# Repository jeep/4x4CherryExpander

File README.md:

# 4x4CherryExpander
4x4 Cherry MX expansion board.

This is the schematic and brd file for a 4x4 matrix of Cherry MX keys with an MCP2300x 8 bit IO Expander.

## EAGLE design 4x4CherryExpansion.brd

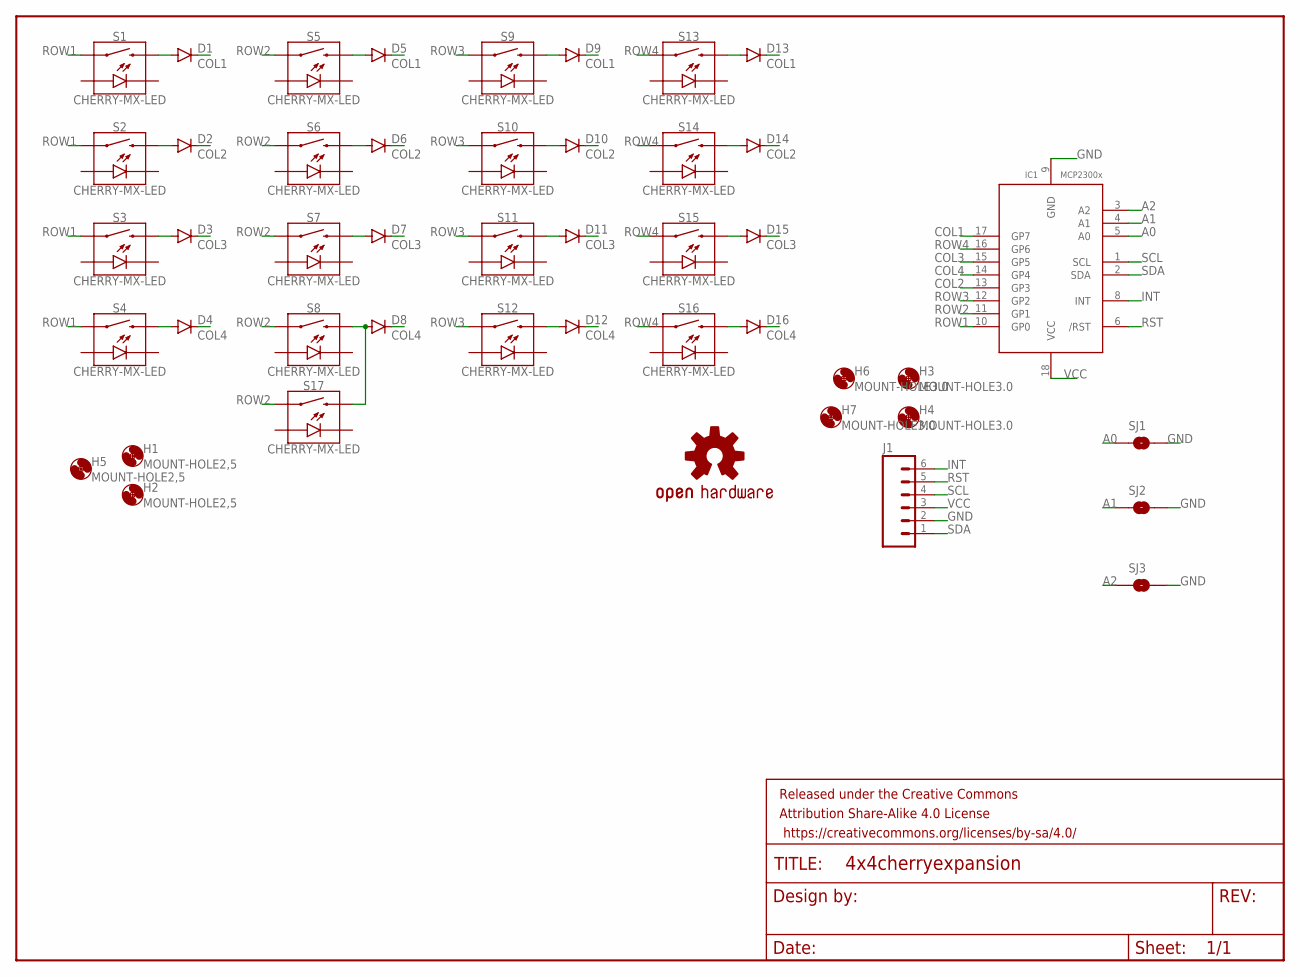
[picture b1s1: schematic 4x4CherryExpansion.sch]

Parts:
D1, D2, D3, D4, D5, D6, D7, D8, D9, D10, D11, D12, D13, D14, D15, D16: DIODEPTH; DIODE-1N4001
FRAME1: FRAME-LETTER; CREATIVE_COMMONS
H1, H2, H5: MOUNT-HOLE2,5; 2,8
H3, H4, H6, H7: MOUNT-HOLE3.0; 3,0
IC1: MCP23008/P; DIL18
J1: M06SILK_FEMALE_PTH; 1X06
LOGO1: OSHW-LOGOL; OSHW-LOGO-L
S1, S2, S3, S4, S5, S6, S7, S8, S9, S10, S11, S12, S13, S14, S15, S16, S17: CHERRY-MX-LED
SJ1, SJ2, SJ3: SOLDERJUMPERNO; SJ_2S-NO

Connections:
A0: IC1.5 (A0), SJ1.1
A1: IC1.4 (A1), SJ2.1
A2: IC1.3 (A2), SJ3.1
COL1: D1.C, D5.C, D9.C, D13.C, IC1.17 (GP7)
COL2: D2.C, D6.C, D10.C, D14.C, IC1.13 (GP3)
COL3: D3.C, D7.C, D11.C, D15.C, IC1.15 (GP5)
COL4: D4.C, D8.C, D12.C, D16.C, IC1.14 (GP4)
GND: IC1.9 (GND), J1.2, SJ1.2, SJ2.2, SJ3.2
INT: IC1.8 (INT), J1.6
unnamed: D9.A, S9.S2
unnamed: D10.A, S10.S2
unnamed: D1.A, S1.S2
unnamed: D11.A, S11.S2
unnamed: D12.A, S12.S2
unnamed: D13.A, S13.S2
unnamed: D14.A, S14.S2
unnamed: D3.A, S3.S2
unnamed: D2.A, S2.S2
unnamed: D15.A, S15.S2
unnamed: D16.A, S16.S2
unnamed: D8.A, S8.S2, S17.S2
unnamed: D4.A, S4.S2
unnamed: D5.A, S5.S2
unnamed: D6.A, S6.S2
unnamed: D7.A, S7.S2
ROW1: IC1.10 (GP0), S1.S1, S2.S1, S3.S1, S4.S1
ROW2: IC1.11 (GP1), S5.S1, S6.S1, S7.S1, S8.S1, S17.S1
ROW3: IC1.12 (GP2), S9.S1, S10.S1, S11.S1, S12.S1
ROW4: IC1.16 (GP6), S13.S1, S14.S1, S15.S1, S16.S1
RST: IC1.6 (/RST), J1.5
SCL: IC1.1 (SCL), J1.4
SDA: IC1.2 (SDA), J1.1
VCC: IC1.18 (VCC), J1.3

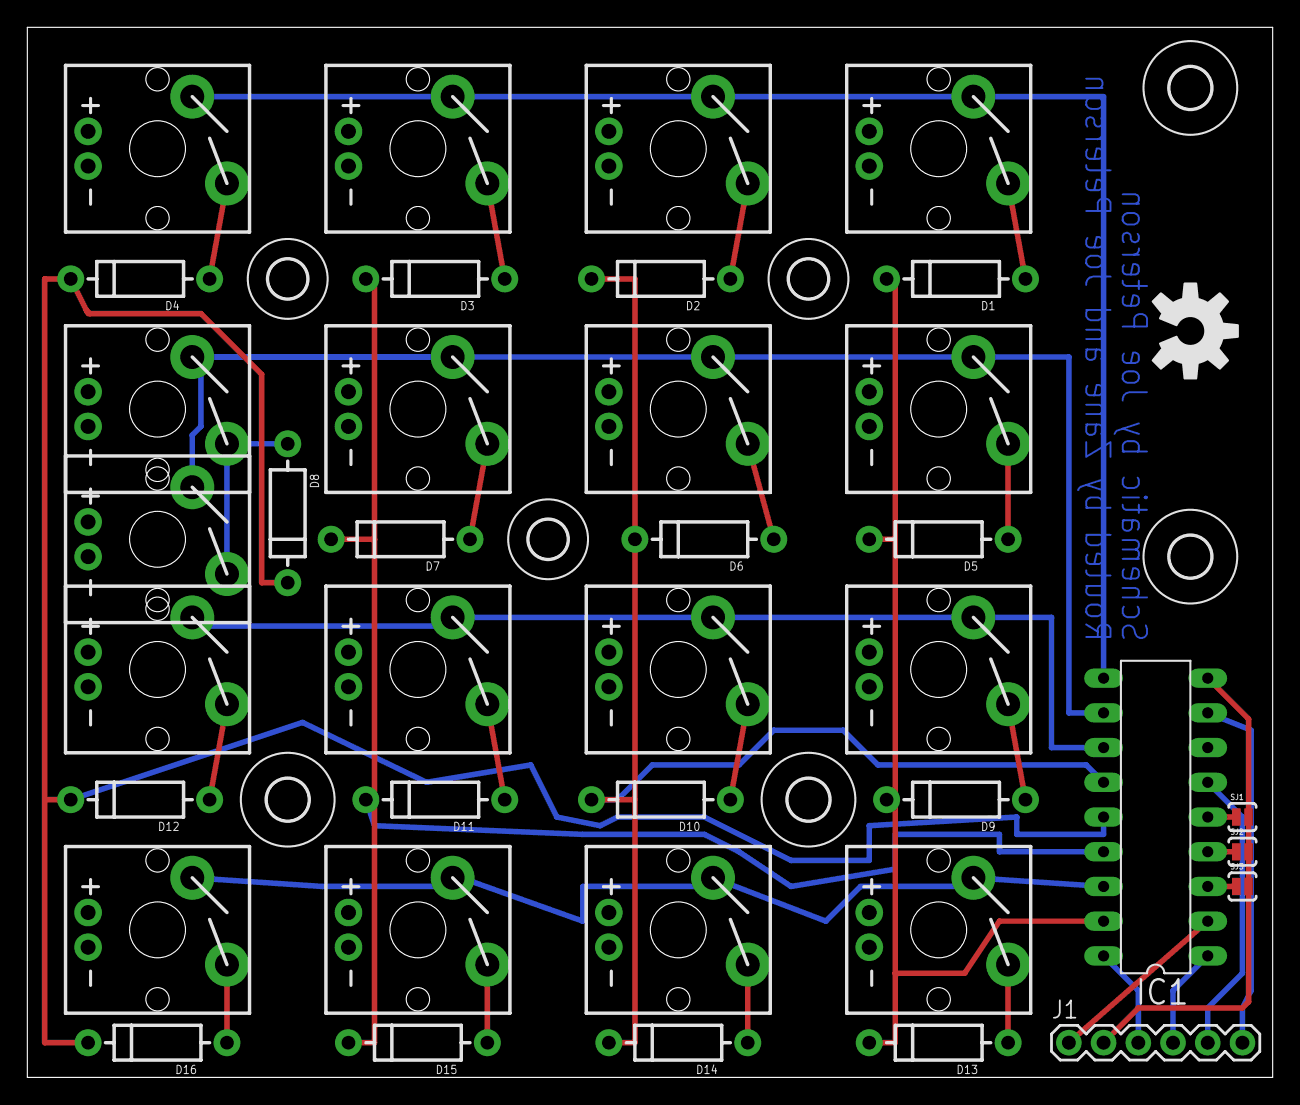
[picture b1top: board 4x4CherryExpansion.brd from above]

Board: 2 copper layers, 91.1 x 76.8 mm, 47 parts (0 on the bottom side), 33 nets.

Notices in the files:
parts and their libraries:
SparkFun-Aesthetics: Licensing: Creative Commons ShareAlike 4.0 International - https://creativecommons.org/licenses/by-sa/4.0
SparkFun-Aesthetics: Released under the Creative Commons Attribution Share-Alike 4.0 License
SparkFun-Aesthetics: https://creativecommons.org/licenses/by-sa/4.0
